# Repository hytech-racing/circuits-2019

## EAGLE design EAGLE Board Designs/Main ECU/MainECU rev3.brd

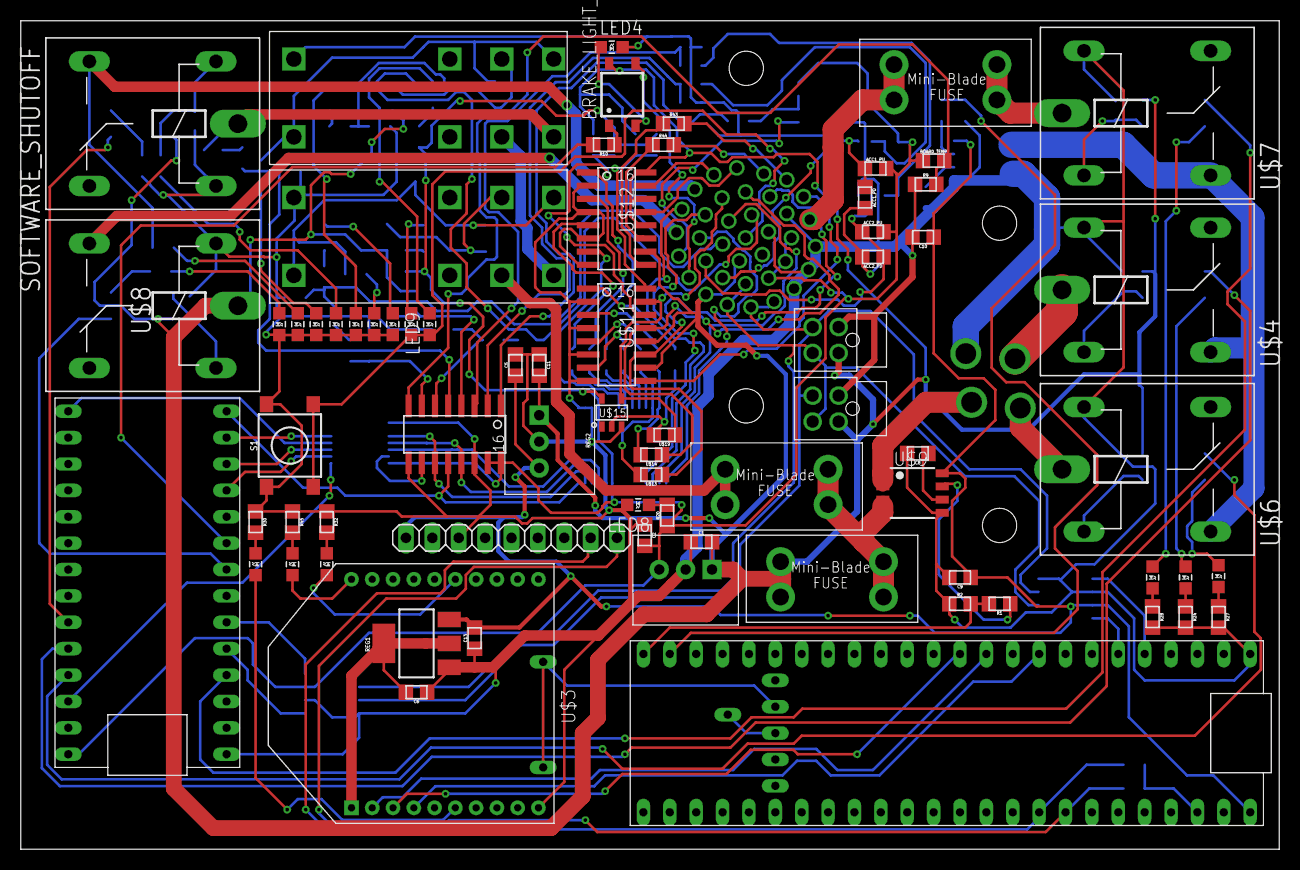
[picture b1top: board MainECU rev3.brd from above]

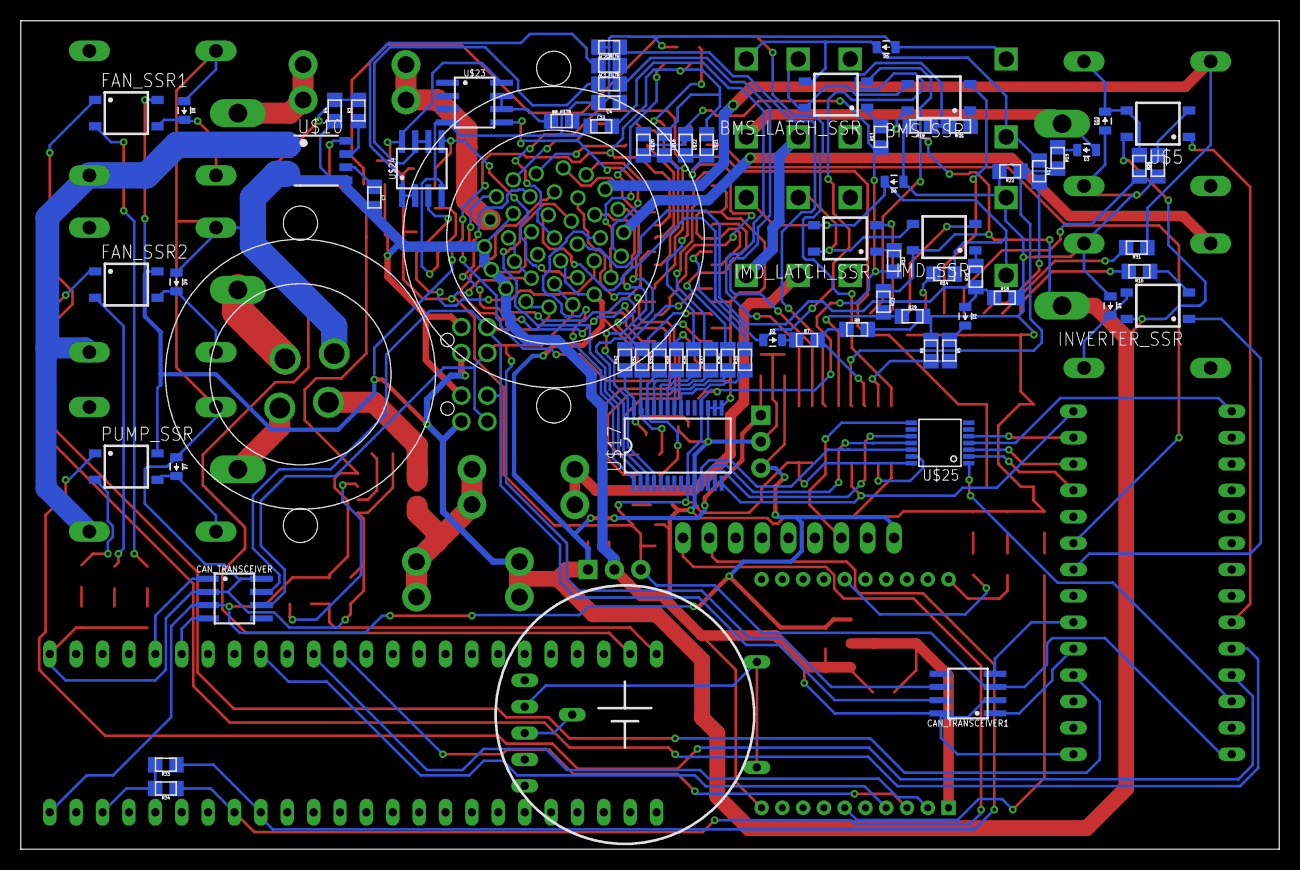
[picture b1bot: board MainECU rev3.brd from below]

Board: 2 copper layers, 121.2 x 79.8 mm, 145 parts (72 on the bottom side), 145 nets.

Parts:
5ABOARDFUSE, 5AFUSE, 5ASHUTDOWNFUSE: MINI-BLADE_FUSE_HOLDER
AC1_FILTR, AC2_FILTR: 510; 0805
ACC1_PD, ACC1_PU, ACC2_PD, ACC2_PU: 10k; 0805
ADXL345_BREAKOUT: 1X09
BMS_LATCH_SSR: CPC1002N; SOP04
BMS_SSR: CPC1002N; SOP04
BOARD_TEMP: THERMISTOR_NCP210805; 0805
BRAKE_LIGHT_SSR: CPC1002N; SOP04
BR_FILTR: 100; 0805
C1, C2, C11, C13: 10uF; 0805
C3, C4: 22µ; 0805
C5, C6: 1uF; 0805
C7, C8: 0805
C9, C10: 0.1uF; 0805
C12: 2.2µ; 0805
CAN_TRANSCEIVER, CAN_TRANSCEIVER1: MCP2551; SOIC-08
D1, D2, D3, D4, D5, D6, D7, D8, D9, D10: DIODE0805; 0805_D
FAN_SSR1, FAN_SSR2: CPC1002N; SOP04
IMD_LATCH_SSR: CPC1002N; SOP04
IMD_SHUTDOWN, IMD_SHUTDOWN1: G2RL-2-DC12; G2RL-2
IMD_SSR: CPC1002N; SOP04
INVERTER_SSR: CPC1002N; SOP04
LED1, LED2: White; LED-805
LED3, LED7, LED11: Green; LED-805
LED4, LED6, LED10, LED12, LED13, LED16: Red; LED-805
LED5, LED9: Yellow; LED-805
LED8: Purple; LED-805
LED14: Blue; LED-805
LED17, LED18: RED; LED-805
PUMP_SSR: CPC1002N; SOP04
R1, R3: 1K; 0805
R2, R4: 2K; 0805
R5, R7, R15, R23: 43k; 0805
R6, R8, R22, R29: 12k; 0805
R9, R19: 10k; 0805
R10, R16: 43; 0805
R11: 150; 0805
R12, R13, R24, R27, R28, R30: 33; 0805
R14, R21: 2k; 0805
R17: 20k; 0805
R18: 2.2k; 0805
R20, R35, R36, R37, R38, R39, R40, R41, R42: 270; 0805
R25: 330; 0805
R26: 1.2K; 0805
R31: 6.8k; 0805
R32: 1.2k; 0805
R33, R34: 4.7k; 0805
R43, R44, R45: 0; 0805
REG, REG2: 5V; OKI-78SR
REG1: TLV1117LV33; SOT223
S1: TACTILE_SWITCH_SMD_6.2MM_TALL
SOFTWARE_SHUTOFF: G5LE; ZF112
U$1: TEENSY_3.2_SIMPLE
U$2: TEENSY_3.5_EXT
U$3: XBEE
U$4, U$6, U$7, U$8: G5LE; ZF112
U$5: CPC1002N; SOP04
U$9, U$10: ACS715_CURRENT_SENSOR; SOP8
U$11, U$12: TLP291-4; SOIC-16
U$13, U$14, U$16, U$19, U$20, U$21, U$22: JUMPER; 0805
U$15: SN74LV1T34; SOT-23-5
U$17: MCP23S17SSOP28; SSOP28
U$18: MCP3208SOIC; SOIC-16
U$23, U$24: MCP6002SOIC; SOIC-08
U$25: TXB0104TSSOP; TSSOP-14
U$26: CR-2450/G1AN
X1: CONNECTOR-37; AUTOSPORT_14-35
X2: CONNECTOR-4AUTOSPORT; AUTOSPORT_12-04
X3, X4: CONNECTOR-4NANO-FIT-VERTICAL-4; NANO-FIT_VERTICAL-4

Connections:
3.3V: R33.2, R34.2, U$2.3.3V
3.3V_MAIN_TEENSY: U$1.3.3V, U$25.1
12VIN: U$9.1, U$9.2, X2.P$1
12VSUPPLY_READ: R23.2, R29.1, U$18.4
12VUNFUSED: 5ABOARDFUSE.L1, 5ABOARDFUSE.L2, 5ASHUTDOWNFUSE.L1, 5ASHUTDOWNFUSE.L2, U$9.3, U$9.4
+5V: ACC1_PU.2, ACC2_PU.2, BOARD_TEMP.1, C2.2, CAN_TRANSCEIVER1.3, R12.2, R13.1, R20.1, REG.3, U$1.VIN, U$15.5, U$17.9, U$17.18, U$18.15, U$18.16, U$20.1, U$22.1, U$23.8, U$24.8, U$25.14, X1.P$27, X1.P$28, X1.P$29
+12V: 5ABOARDFUSE.R1, 5ABOARDFUSE.R2, BMS_SSR.4, BRAKE_LIGHT_SSR.4, C1.2, C11.2, FAN_SSR1.4, FAN_SSR2.4, IMD_SSR.4, INVERTER_SSR.4, PUMP_SSR.4, R23.1, REG.1, REG2.1, U$5.4, U$8.P, U$11.10, U$11.12, U$12.10, U$12.12, U$12.14, U$12.16, U$16.1, U$21.1, X1.P$10, X1.P$34, X3.P$1, X4.P$1
BMS_COIL_PWR: BMS_LATCH_SSR.3, D5.C, IMD_SHUTDOWN1.4, IMD_SHUTDOWN1.COIL-, R17.1
BMS_OK: D2.A, R11.2, R19.1, X1.P$31
BMS_OK_READ: R7.2, R8.1, U$18.6
BMS_PWR_STEP: BMS_LATCH_SSR.4, BMS_SSR.3, IMD_SHUTDOWN1.3
BRAKE_LIGHT: BRAKE_LIGHT_SSR.3, X1.P$9
BRAKE_LIGHT_CTRL: R10.2, U$1.D7(RX3)
CANH: CAN_TRANSCEIVER.7, CAN_TRANSCEIVER1.7, X1.P$12, X1.P$13, X3.P$4, X4.P$4
CANL: CAN_TRANSCEIVER.6, CAN_TRANSCEIVER1.6, X1.P$11, X1.P$26, X3.P$3, X4.P$3
COOLINGSENSE: R3.2, R4.2, U$2.A12
CS1_5V: U$18.10, U$25.13
CS1_TEENSY: U$1.D9(RX2), U$25.2
CS2_5V: U$17.11, U$25.12
CS2_TEENSY: U$1.D10(TX2), U$25.3
CURRENTSENSE2: U$4.S, U$6.S, U$7.S, U$10.1, U$10.2
DASH_CTRL1: R35.1, U$17.21
DASH_CTRL2: R36.1, U$17.22
DASH_CTRL3: R37.1, U$17.23
DASH_CTRL4: R38.1, U$17.24
DASH_CTRL5: R39.1, U$17.25
DASH_CTRL6: R40.1, U$13.2, U$17.26
DASH_CTRL7: R41.1, U$14.2, U$17.27
DASH_CTRL8: R42.1, U$15.2, U$17.28, U$19.2
DASH_CTRL9: U$17.1, X1.P$23
DASH_CTRL10: U$17.2, X1.P$32
DASH_CTRL11: U$17.3, X1.P$6
DASH_CTRL12: U$17.4, X1.P$22
DASH_IO1: R43.2, X1.P$1
DASH_IO2: R44.2, X1.P$2
DASH_IO3: U$12.13, X1.P$3
DASH_IO4: U$12.15, X1.P$4
DASH_IO5: U$11.9, X1.P$18
DASH_IO6: U$11.11, U$13.1, X1.P$19
DASH_IO7: U$11.13, U$14.1, X1.P$20
DASH_IO8: U$11.15, U$15.4, U$19.1, X1.P$21
ECUSENSE: R1.2, R2.2, U$2.A13
FAN1-: 5AFUSE.R1, 5AFUSE.R2, U$7.P
FAN2-: U$4.P, X2.P$3
GND: ACC1_PD.2, ACC2_PD.2, ADXL345_BREAKOUT.3, C1.1, C2.1, C3.2, C4.2, C5.2, C6.1, C7.2, C8.2, C9.2, C10.2, C11.1, C12.1, C13.1, CAN_TRANSCEIVER.2, CAN_TRANSCEIVER.8, CAN_TRANSCEIVER1.2, CAN_TRANSCEIVER1.8, D4.A, D5.A, D6.A, D7.A, D8.A, D9.A, D10.A, IMD_SHUTDOWN.COIL+, IMD_SHUTDOWN1.COIL+, LED3.C, LED4.C, LED5.C, LED6.C, LED7.C, LED8.C, LED9.C, LED17.C, LED18.C, R2.1, R4.1, R6.2, R8.2, R9.1, R18.2, R19.2, R22.2, R24.2, R25.1, R27.2, R28.2, R29.2, R30.1, R32.1, R45.1, REG.2, REG1.1, REG2.2, S1.B1, S1.B2, SOFTWARE_SHUTOFF.1, U$1.GND, U$2.GND, U$3.10, U$4.1, U$6.1, U$7.1, U$8.2, U$9.5, U$10.3, U$10.4, U$10.5, U$11.2, U$11.4, U$11.6, U$11.8, U$12.2, U$12.4, U$12.6, U$12.8, U$15.3, U$17.10, U$17.15, U$17.16, U$17.17, U$18.9, U$18.14, U$23.4, U$24.4, U$25.8, X1.P$14, X1.P$15, X1.P$16, X1.P$30, X1.P$36, X2.P$4, X3.P$2, X4.P$2
IMD_COIL_PWR: D6.C, IMD_LATCH_SSR.3, IMD_SHUTDOWN.4, IMD_SHUTDOWN.COIL-, R14.1
IMD_PWR_STEP: IMD_LATCH_SSR.4, IMD_SHUTDOWN.3, IMD_SSR.3
INVERTER_CTRL: INVERTER_SSR.1, U$1.D6
INVERTER_SUPPLY: U$8.S, X1.P$7
LATCH_EXT_BUTTON: LED1.C, LED2.C, S1.A1, S1.A2, X1.P$37
MISO_TEENSY: U$1.D12, U$17.14, U$18.12
MOSI_5V: U$17.13, U$18.11, U$25.10
MOSI_TEENSY: U$1.D11, U$25.5
unnamed: 5AFUSE.L1, 5AFUSE.L2, X1.P$17
unnamed: IMD_LATCH_SSR.2, LED1.A
unnamed: R1.1, U$9.7
unnamed: D7.C, PUMP_SSR.3, U$6.2
unnamed: IMD_LATCH_SSR.1, R12.1
unnamed: R3.1, U$10.7
unnamed: BRAKE_LIGHT_SSR.2, LED4.A
unnamed: C8.1, U$9.6
unnamed: BMS_SSR.2, LED3.A
unnamed: D1.C, R5.1
unnamed: D2.C, R7.1
unnamed: BMS_LATCH_SSR.1, R13.2
unnamed: CAN_TRANSCEIVER.4, U$2.D4(CANRX)
unnamed: CAN_TRANSCEIVER.1, U$2.D3(CANTX)
unnamed: CAN_TRANSCEIVER1.4, U$1.D4(CANRX)
unnamed: BMS_LATCH_SSR.2, LED2.A
unnamed: BRAKE_LIGHT_SSR.1, R10.1
unnamed: BMS_SSR.1, R11.1
unnamed: LED5.A, R14.2
unnamed: D8.C, FAN_SSR1.3, U$7.2
unnamed: D9.C, FAN_SSR2.3, U$4.2
unnamed: CAN_TRANSCEIVER1.1, U$1.D3(CANTX)
unnamed: AC2_FILTR.1, U$24.1, U$24.2
unnamed: AC1_FILTR.1, U$24.6, U$24.7
unnamed: BR_FILTR.1, U$23.6, U$23.7
unnamed: D4.C, INVERTER_SSR.3, U$8.1
unnamed: INVERTER_SSR.2, R16.1
unnamed: LED6.A, R16.2
unnamed: LED8.A, R20.2
unnamed: LED16.C, R24.1
unnamed: IMD_SSR.1, R21.2
unnamed: LED7.A, R17.2
unnamed: D3.C, R15.1
unnamed: IMD_SSR.2, LED9.A
unnamed: LED14.C, R45.2
unnamed: LED13.C, R28.1
unnamed: LED12.C, R27.1
unnamed: LED12.A, PUMP_SSR.2
unnamed: FAN_SSR2.2, LED16.A
unnamed: LED18.A, R31.2
unnamed: U$2.3.3V_2, U$26.+_0, U$26.+_1
unnamed: FAN_SSR1.2, LED13.A
unnamed: D10.C, R26.1, SOFTWARE_SHUTOFF.2, U$5.3
unnamed: R25.2, U$5.2
unnamed: LED11.C, R30.2
unnamed: LED17.A, R26.2
unnamed: LED11.A, U$3.6
unnamed: C7.1, U$10.6
unnamed: LED10.A, U$3.15
unnamed: LED10.C, R32.2
unnamed: R35.2, U$12.7
unnamed: R36.2, U$12.5
unnamed: R37.2, U$12.3
unnamed: R38.2, U$12.1
unnamed: R39.2, U$11.7
unnamed: R40.2, U$11.5
unnamed: R41.2, U$11.3
unnamed: R42.2, U$11.1
unnamed: R43.1, U$12.9
unnamed: R44.1, U$12.11
unnamed: U$11.16, U$16.2, U$20.2
unnamed: U$11.14, U$21.2, U$22.2
unnamed: LED14.A, U$3.20
unnamed: U$2.GND_2, U$26.-
OKHS: D1.A, R18.1, R21.1, X1.P$33
OKHS_READ: R5.2, R6.1, U$18.7
PUMP1-: U$6.P, X2.P$2
READ_ACCEL1: AC1_FILTR.2, C4.1, U$18.2
READ_ACCEL2: AC2_FILTR.2, C3.1, U$18.3
READ_BRAKE: BR_FILTR.2, C12.2, U$18.1
RELAY_CTRL1: PUMP_SSR.1, U$1.A9
RELAY_CTRL2: FAN_SSR1.1, U$1.D2
RELAY_CTRL3: FAN_SSR2.1, U$1.A8
SCK_5V: U$17.12, U$18.13, U$25.11
SCK_TEENSY: U$1.D13, U$25.4
SCL: ADXL345_BREAKOUT.9, R34.1, U$2.A5
SDA: ADXL345_BREAKOUT.8, R33.1, U$2.A4
SHUTDOWN_A: 5ASHUTDOWNFUSE.R1, 5ASHUTDOWNFUSE.R2, IMD_SHUTDOWN.6
SHUTDOWN_B: IMD_SHUTDOWN.5, IMD_SHUTDOWN1.6
SHUTDOWN_C: D3.A, IMD_SHUTDOWN1.5, SOFTWARE_SHUTOFF.P
SHUTDOWN_D: R31.1, SOFTWARE_SHUTOFF.S, X1.P$5
SHUTDOWN_OUT_READ: R15.2, R22.1, U$18.5
SIGNAL_ACCEL1: ACC1_PD.1, ACC1_PU.1, U$24.5, X1.P$25
SIGNAL_ACCEL2: ACC2_PD.1, ACC2_PU.1, U$24.3, X1.P$24
SIGNAL_BRAKE: U$23.5, X1.P$8
SOFTWARE_SHUTDOWN: U$1.A7, U$5.1
TELEMETRY5V: ADXL345_BREAKOUT.1, C5.1, C9.1, C10.1, C13.2, CAN_TRANSCEIVER.3, REG1.3, REG2.3, U$2.VIN, U$9.8, U$10.8
TEMPSENSE: BOARD_TEMP.2, R9.2, U$18.8
VCC: C6.2, REG1.2, REG1.4, U$3.1
XB8: U$2.D7(RX3), U$3.4
XBDI: U$2.D10(TX2), U$3.3
XBDO: U$2.D9(RX2), U$3.2

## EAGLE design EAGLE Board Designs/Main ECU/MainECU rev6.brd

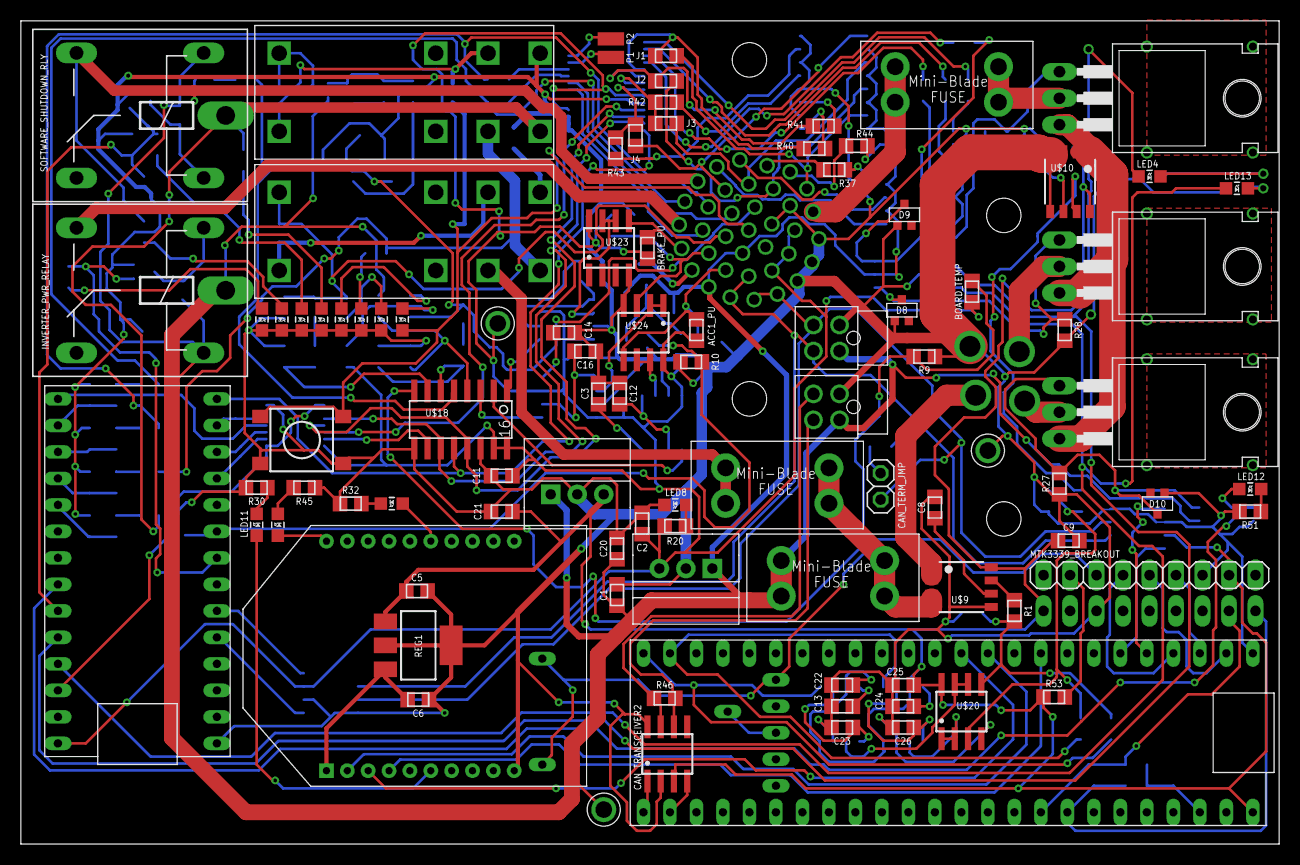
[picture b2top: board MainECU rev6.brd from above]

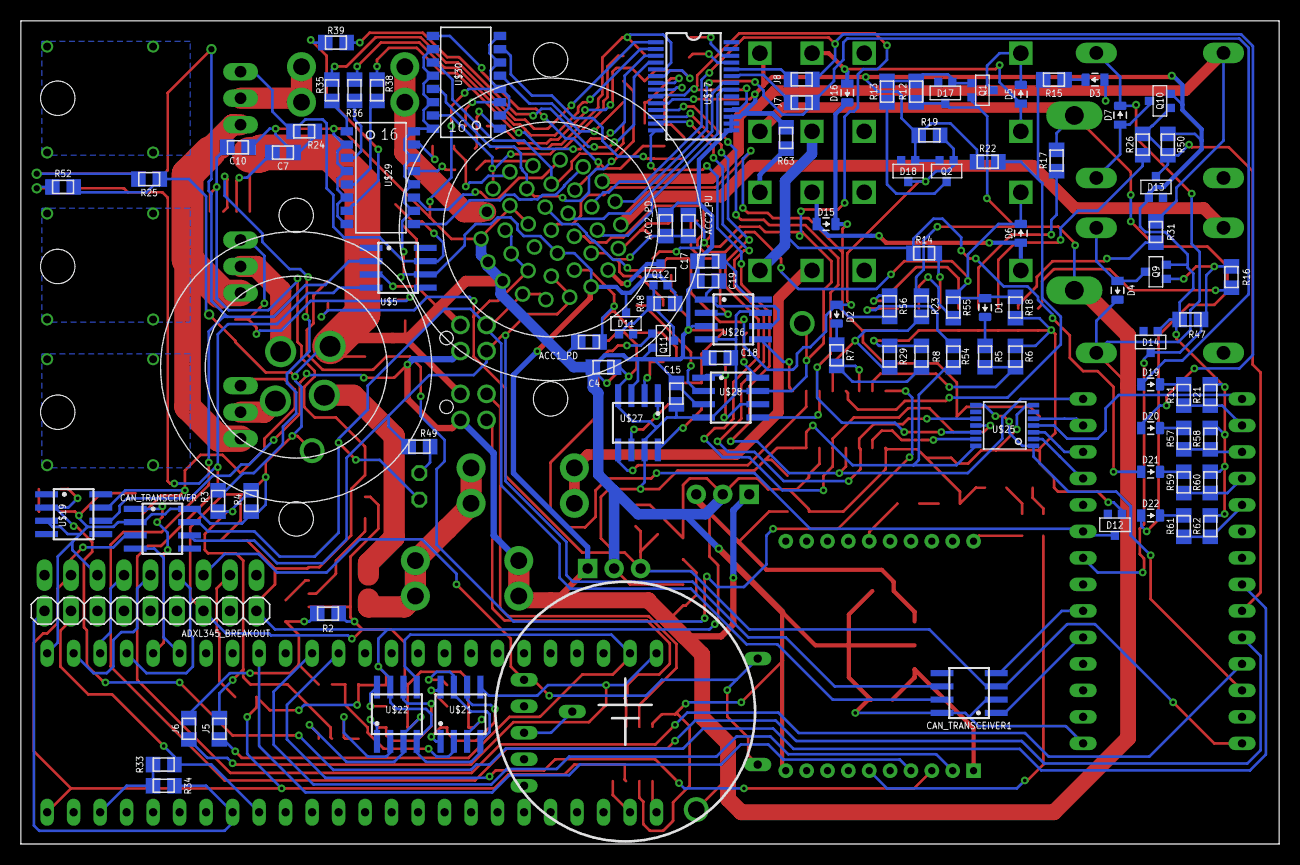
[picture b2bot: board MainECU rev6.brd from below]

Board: 2 copper layers, 120.6 x 78.9 mm, 196 parts (101 on the bottom side), 169 nets.

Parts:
5ABOARDFUSE, 5AFUSE, 5ASHUTDOWNFUSE: MINI-BLADE_FUSE_HOLDER
ACC1_PD, ACC1_PU, ACC2_PD, ACC2_PU: 10k; 0805
ADXL345_BREAKOUT: 1X09
BMS_SHUTDOWN_RLY: RT424012; RELAY_DPDT
BOARD_TEMP: THERMISTOR_NCP210805; 0805
BRAKE_PU: 10k; 0805
C1, C2, C20, C21: 10uF; 0805
C3, C7, C8, C14, C17: 47nF; 0805
C4, C12, C15, C16, C18, C19, C22, C23, C25, C26: .1uF; 0805
C5, C6, C11: 1uF; 0805
C9, C10: 0.1uF; 0805
C13, C24: 470pF; 0805
CAN_TERM_JMP: M02_SLIM; 1X02_SLIM
CAN_TRANSCEIVER, CAN_TRANSCEIVER1, CAN_TRANSCEIVER2: MCP2551; SOIC-08
D1, D2, D3, D4, D5, D6, D7, D15, D16, D19, D20, D21, D22: TS4148 RYG; 0805_D
D8, D9, D10, D11, D12, D13, D14, D17, D18: MMBZ5246BLT1G; SOT23
IMD_SHUTDOWN_RLY: RT424009; RELAY_DPDT
INVERTER_PWR_RELAY: G5LE; ZF112
J1, J2, J3, J4, J5, J6, J7, J8: JUMPER; 0805
LED1: White; LED-805
LED3, LED7, LED11: Green; LED-805
LED4, LED6, LED10, LED12, LED13, LED17, LED18: Red; LED-805
LED5, LED9: Yellow; LED-805
LED8: Purple; LED-805
LED14: Blue; LED-805
MTK3339_BREAKOUT: 1X09
P1, P2: SOLDER_PAD; SOLDER_PAD_XSMALL
Q1, Q12: P-CHANNEL_MOSFET_DMP3099L-7; SOT23
Q2, Q9, Q10, Q11: SOT23
R1, R3: 1K; 0805
R2, R4: 2K; 0805
R5, R7, R11, R15, R23, R57, R59, R61: 43k; 0805
R6, R8, R21, R22, R29, R58, R60, R62: 12k; 0805
R9, R10, R12, R19, R24, R27, R28, R47, R48, R50, R53: 10k; 0805
R13: 1k; 0805
R14, R18, R55: 2k; 0805
R16, R25, R32, R51, R52: 1.2k; 0805
R17: 20k; 0805
R20: 270; 0805
R26: 1.2K; 0805
R30, R56: 33; 0805
R31: 6.8k; 0805
R33, R34: 4.7k; 0805
R35, R36, R38, R39, R40, R41, R42, R43: 150; 0805
R37, R44, R45: 0; 0805
R46, R49: 120; 0805
R54: 5.1k; 0805
R63: 20; 0805
REG, REG3: 5V; OKI-78SR
REG1: LM3940; SOT223
S1: TACTILE_SWITCH_SMD_6.2MM_TALL
SOFTWARE_SHUTDOWN_RLY: G5LE; ZF112
U$1: TEENSY_3.2_SIMPLE
U$2: TEENSY_3.5_EXT
U$3: XBEE
U$4, U$6, U$7: N-CHANNEL_MOSFET_FQP30N06L; TO-220-H-HOLE
U$5, U$19: MC34152; SOIC-08
U$8, U$11, U$12: TEST_POINT
U$9, U$10: ACS715_CURRENT_SENSOR; SOP8
U$16: CR-2450/G1AN
U$17: MCP23S17SSOP28; SSOP28
U$18: MCP3208SOIC; SOIC-16
U$20, U$23, U$24: MCP6002SOIC; SOIC-08
U$21, U$22, U$26, U$27, U$28: SOIC-08
U$25: TXB0104TSSOP; TSSOP-14
U$29, U$30: TLP291-4; 11-11F1
X1: CONNECTOR-37; AUTOSPORT_14-35
X2: CONNECTOR-4AUTOSPORT; AUTOSPORT_12-04
X3, X4: CONNECTOR-4NANO-FIT-VERTICAL-4; NANO-FIT_VERTICAL-4

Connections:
3.3V: R33.2, R34.2, U$2.3.3V
3.3V_MAIN_TEENSY: U$1.3.3V, U$25.1, U$25.8
12VIN: U$9.1, U$9.2, X2.P$1
12VSUPPLY_READ: R23.2, R29.1, U$18.4
12VUNFUSED: 5ABOARDFUSE.L1, 5ABOARDFUSE.L2, 5ASHUTDOWNFUSE.L1, 5ASHUTDOWNFUSE.L2, U$9.3, U$9.4
+5V: ACC1_PU.2, ACC2_PU.2, BOARD_TEMP.1, BRAKE_PU.2, C2.2, C4.1, C11.2, C15.1, C18.1, CAN_TRANSCEIVER1.3, R20.1, R54.1, REG.3, U$1.VIN, U$11.P$1, U$17.9, U$17.18, U$18.15, U$18.16, U$23.8, U$24.8, U$25.14, U$26.4, U$26.7, U$27.4, U$27.7, U$28.4, U$28.7, X1.P$27, X1.P$28, X1.P$29
+12V: 5ABOARDFUSE.R1, 5ABOARDFUSE.R2, C1.2, C20.2, D4.C, D7.C, D11.3, D17.3, INVERTER_PWR_RELAY.1, INVERTER_PWR_RELAY.P, Q1.2, Q12.2, R12.1, R23.1, R48.1, REG.1, REG3.1, SOFTWARE_SHUTDOWN_RLY.2, U$5.6, U$8.P$1, U$19.6, U$29.10, U$29.12, U$29.14, U$29.16, U$30.10, U$30.12, U$30.14, U$30.16, X1.P$10, X1.P$34, X3.P$1, X4.P$1
BMS_OK: D2.A, D18.3, Q2.1, R19.1, R56.1, X1.P$31
BMS_OK_READ: R7.2, R8.1, U$18.6
BMS_OK_SW: BMS_SHUTDOWN_RLY.COIL+, D5.C, Q1.3
BMS_PWR_STEP: BMS_SHUTDOWN_RLY.3, BMS_SHUTDOWN_RLY.COIL-, D5.A, D16.A
BRAKE_LIGHT: Q12.3, X1.P$9
BRAKE_LIGHT_CTRL: D12.3, Q11.1, R10.2, U$1.D7(RX3)
CANH: CAN_TERM_JMP.1, CAN_TRANSCEIVER.7, CAN_TRANSCEIVER1.7, X1.P$12, X1.P$13, X3.P$4
CANL: CAN_TRANSCEIVER.6, CAN_TRANSCEIVER1.6, R49.1, X1.P$11, X1.P$26, X3.P$3
COOLINGSENSE: J5.2, R3.2, R4.2, U$20.3
COOLINGSENSE_FILT: J5.1, U$2.A12, U$22.5
CS1_5V: U$18.10, U$25.13
CS1_TEENSY: U$1.D9(RX2), U$25.2
CS2_5V: U$17.11, U$25.12
CS2_TEENSY: U$1.D10(TX2), U$25.3
CURRENTSENSE2: U$4.3, U$6.3, U$7.3, U$10.1, U$10.2
DASH11_READ: R11.2, R21.1, U$1.A0
DASH12_READ: R57.2, R58.1, U$1.A1
DASH_1_EXTERN: R44.2, X1.P$1
DASH_1_INTER: R35.1, U$17.1
DASH_2_EXTERN: R37.2, X1.P$2
DASH_2_INTER: R36.1, U$17.2
DASH_3_EXTERN: U$29.11, X1.P$3
DASH_3_INTER: R38.1, U$17.3
DASH_4_EXTERN: U$29.9, X1.P$4
DASH_4_INTER: R39.1, U$17.4
DASH_5_EXTERN: J1.1, U$30.15, X1.P$18
DASH_5_INTER: J1.2, R40.1, U$17.5
DASH_6_EXTERN: J2.1, U$30.13, X1.P$19
DASH_6_INTER: J2.2, R41.1, U$17.6
DASH_7_EXTERN: J3.1, U$30.11, X1.P$20
DASH_7_INTER: J3.2, R42.1, U$17.7
DASH_8_EXTERN: J4.1, U$30.9, X1.P$21
DASH_8_INTER: J4.2, R43.1, U$17.8
DASH_9_EXTERN: U$17.21, X1.P$23
DASH_10_EXTERN: U$17.22, X1.P$32
DASH_11_EXTERN: D19.A, J7.1, X1.P$6
DASH_11_INTER: J7.2, U$17.23
DASH_12_EXTERN: D20.A, J8.1, X1.P$22
DASH_12_INTER: J8.2, U$17.24
ECUSENSE: J6.2, R1.2, R2.2, U$20.5
ECUSENSE_FILT: J6.1, U$2.A13, U$21.5
FAN1-: 5AFUSE.R1, 5AFUSE.R2, U$7.2
FAN1CONTROL: LED4.A, U$1.A8, U$5.2
FAN1DRIVE: D9.3, R24.2, U$5.7, U$7.1
FAN2-: U$4.2, X2.P$3
FAN2CONTROL: LED13.A, U$1.A9, U$5.4
FAN2DRIVE: D8.3, R28.2, U$4.1, U$5.5
GND: ACC1_PD.2, ACC2_PD.2, ADXL345_BREAKOUT.3, BMS_SHUTDOWN_RLY.4, C1.1, C2.1, C3.2, C4.2, C5.2, C6.1, C7.2, C8.2, C9.2, C10.2, C11.1, C12.1, C13.2, C14.2, C15.2, C16.1, C17.2, C18.2, C19.1, C20.1, C21.1, C22.2, C23.1, C24.2, C25.2, C26.1, CAN_TRANSCEIVER.2, CAN_TRANSCEIVER.8, CAN_TRANSCEIVER1.2, CAN_TRANSCEIVER1.8, CAN_TRANSCEIVER2.2, CAN_TRANSCEIVER2.8, D8.1, D9.1, D10.1, D12.1, D13.1, D14.1, D18.1, LED3.C, LED5.C, LED6.C, LED7.C, LED8.C, LED9.C, LED17.C, LED18.C, MTK3339_BREAKOUT.7, Q2.2, Q9.2, Q10.2, Q11.2, R2.1, R4.1, R6.2, R8.2, R9.1, R10.1, R18.2, R19.2, R21.2, R22.2, R24.1, R25.2, R27.1, R28.1, R29.2, R30.1, R32.1, R45.1, R47.2, R50.2, R51.2, R52.2, R58.2, R60.2, R62.2, R63.2, REG.2, REG1.2, REG1.4, REG3.2, S1.B1, S1.B2, U$1.GND, U$2.GND, U$3.10, U$5.3, U$9.5, U$10.3, U$10.4, U$10.5, U$12.P$1, U$17.10, U$17.15, U$17.16, U$17.17, U$18.9, U$18.14, U$19.3, U$20.4, U$21.3, U$22.3, U$23.4, U$24.4, U$25.7, U$26.3, U$27.3, U$28.3, U$29.2, U$29.4, U$29.6, U$29.8, U$30.2, U$30.4, U$30.6, U$30.8, X1.P$14, X1.P$15, X1.P$16, X1.P$30, X1.P$36, X2.P$4, X3.P$2, X4.P$2
IMD_PWR_STEP: D6.A, D15.A, IMD_SHUTDOWN_RLY.3, IMD_SHUTDOWN_RLY.COIL-
INVERTER_CTRL: D14.3, Q9.1, R16.1, R47.1, U$1.D6
INVERTER_SUPPLY: INVERTER_PWR_RELAY.S, X1.P$7
LATCH_EXT_BUTTON: D15.C, D16.C, LED1.C, S1.A1, S1.A2, X1.P$37
MISO_TEENSY: U$1.D12, U$17.14, U$18.12
MOSI_5V: U$17.13, U$18.11, U$25.10
MOSI_TEENSY: U$1.D11, U$25.5
MTK3339_DIN: MTK3339_BREAKOUT.6, U$2.D1(TX1)
MTK3339_DOUT: MTK3339_BREAKOUT.5, U$2.D0(RX1)
MTK3339_FIX: MTK3339_BREAKOUT.4, U$2.D2
unnamed: 5AFUSE.L1, 5AFUSE.L2, X1.P$17
unnamed: LED1.A, R54.2
unnamed: R1.1, U$9.7
unnamed: C12.2, U$27.1, U$27.6
unnamed: D20.C, R57.1
unnamed: R3.1, U$10.7
unnamed: MTK3339_BREAKOUT.2, R53.2
unnamed: C8.1, U$9.6
unnamed: LED3.A, R56.2
unnamed: D1.C, R5.1
unnamed: D2.C, R7.1
unnamed: D17.1, Q1.1, R12.2, R13.2
unnamed: CAN_TRANSCEIVER.4, U$2.D4(CANRX)
unnamed: CAN_TRANSCEIVER.1, U$2.D3(CANTX)
unnamed: CAN_TRANSCEIVER1.4, U$1.D4(CANRX)
unnamed: Q2.3, R13.1
unnamed: CAN_TERM_JMP.2, R49.2
unnamed: D19.C, R11.1
unnamed: LED5.A, R14.2
unnamed: U$20.1, U$20.2, U$22.2
unnamed: C3.1, U$27.8
unnamed: CAN_TRANSCEIVER1.1, U$1.D3(CANTX)
unnamed: U$24.1, U$24.2, U$28.2
unnamed: U$24.6, U$24.7, U$27.2
unnamed: U$23.6, U$23.7, U$26.2
unnamed: LED9.A, R55.2
unnamed: D7.A, Q10.3, SOFTWARE_SHUTDOWN_RLY.1
unnamed: LED6.A, R16.2
unnamed: LED8.A, R20.2
unnamed: R36.2, U$29.3
unnamed: D21.C, R59.1
unnamed: LED7.A, R17.2
unnamed: D3.C, R15.1
unnamed: D22.C, R61.1
unnamed: LED14.C, R45.2
unnamed: C16.2, U$28.1, U$28.6
unnamed: C19.2, U$26.1, U$26.6
unnamed: C14.1, U$28.8
unnamed: U$20.6, U$20.7, U$21.2
unnamed: LED18.A, R31.2
unnamed: C17.1, U$26.8
unnamed: R37.1, U$29.13
unnamed: C23.2, U$21.1, U$21.6
unnamed: C13.1, U$21.8
unnamed: LED11.C, R30.2
unnamed: LED17.A, R26.2
unnamed: LED11.A, U$3.6
unnamed: C7.1, U$10.6
unnamed: LED10.A, U$3.15
unnamed: LED10.C, R32.2
unnamed: R35.2, U$29.1
unnamed: R38.2, U$29.5
unnamed: R39.2, U$29.7
unnamed: R40.2, U$30.1
unnamed: R41.2, U$30.3
unnamed: R42.2, U$30.5
unnamed: R43.2, U$30.7
unnamed: D11.1, Q11.3, Q12.1, R48.2
unnamed: R44.1, U$29.15
unnamed: IMD_SHUTDOWN_RLY.4, R63.1
unnamed: U$2.GND_2, U$16.-
unnamed: CAN_TRANSCEIVER2.4, U$2.A15
unnamed: LED14.A, U$3.20
unnamed: CAN_TRANSCEIVER2.1, U$2.A14
unnamed: D4.A, INVERTER_PWR_RELAY.2, Q9.3
unnamed: C26.2, U$22.1, U$22.6
unnamed: C24.1, U$22.8
unnamed: LED4.C, R25.1
unnamed: LED12.C, R51.1
unnamed: LED13.C, R52.1
unnamed: P1.P$1, U$17.25
unnamed: P2.P$1, U$17.26
OKHS: D1.A, D6.C, IMD_SHUTDOWN_RLY.COIL+, R18.1, R55.1, X1.P$33
OKHS_READ: R5.2, R6.1, U$18.7
PUMP1-: U$6.2, X2.P$2
PUMPCONTROL: LED12.A, U$1.A6, U$19.2
PUMPDRIVE: D10.3, R27.2, U$6.1, U$19.7
READ_ACCEL1: U$18.2, U$27.5
READ_ACCEL2: U$18.3, U$28.5
READ_BRAKE: U$18.1, U$26.5
SCK_5V: U$17.12, U$18.13, U$25.11
SCK_TEENSY: U$1.D13, U$25.4
SCL: ADXL345_BREAKOUT.9, R34.1, U$2.A5
SDA: ADXL345_BREAKOUT.8, R33.1, U$2.A4
SHUTDOWN_A: 5ASHUTDOWNFUSE.R1, 5ASHUTDOWNFUSE.R2, IMD_SHUTDOWN_RLY.6
SHUTDOWN_B: BMS_SHUTDOWN_RLY.6, D21.A, IMD_SHUTDOWN_RLY.5, R14.1
SHUTDOWN_B_READ: R59.2, R60.1, U$1.A2
SHUTDOWN_C: BMS_SHUTDOWN_RLY.5, D22.A, R17.1, SOFTWARE_SHUTDOWN_RLY.P
SHUTDOWN_C_READ: R61.2, R62.1, U$1.A3
SHUTDOWN_D: D3.A, R31.1, SOFTWARE_SHUTDOWN_RLY.S, X1.P$5
SHUTDOWN_OUT_READ: R15.2, R22.1, U$18.5
SIGNAL_ACCEL1: ACC1_PD.1, ACC1_PU.1, U$24.5, X1.P$25
SIGNAL_ACCEL2: ACC2_PD.1, ACC2_PU.1, U$24.3, X1.P$24
SIGNAL_BRAKE: BRAKE_PU.1, U$23.5, X1.P$8
SOFTWARE_SHUTDOWN: D13.3, Q10.1, R26.1, R50.1, U$1.A7
TELEMETRY5V: ADXL345_BREAKOUT.1, C5.1, C9.1, C10.1, C21.2, C22.1, C25.1, CAN_TRANSCEIVER.3, CAN_TRANSCEIVER2.3, MTK3339_BREAKOUT.8, R53.1, REG1.1, REG3.3, U$2.VIN, U$9.8, U$10.8, U$20.8, U$21.4, U$21.7, U$22.4, U$22.7
TELEMETRY_CANH: CAN_TRANSCEIVER2.7, R46.2, X4.P$4
TELEMETRY_CANL: CAN_TRANSCEIVER2.6, R46.1, X4.P$3
TEMPSENSE: BOARD_TEMP.2, R9.2, U$18.8
VBAT_RTC: MTK3339_BREAKOUT.3, U$2.VBAT, U$16.+_0, U$16.+_1
VCC: C6.2, REG1.3, U$3.1
XB8: U$2.D7(RX3), U$3.4
XBDI: U$2.D10(TX2), U$3.3
XBDO: U$2.D9(RX2), U$3.2

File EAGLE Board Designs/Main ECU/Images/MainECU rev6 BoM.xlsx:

Part | Value | Device | Package
5ABOARDFUSE |  | FUSE_MINIBLADE | MINI-BLADE_FUSE_HOLDER
5AFUSE |  | FUSE_MINIBLADE | MINI-BLADE_FUSE_HOLDER
5ASHUTDOWNFUSE |  | FUSE_MINIBLADE | MINI-BLADE_FUSE_HOLDER
ACC1_PD | 10k | RESISTOR0805-RES | 805
ACC1_PU | 10k | RESISTOR0805-RES | 805
ACC2_PD | 10k | RESISTOR0805-RES | 805
ACC2_PU | 10k | RESISTOR0805-RES | 805
ADXL345_BREAKOUT |  | M09 | 1X09
BMS_SHUTDOWN_RLY | RT424012 | RT424012 | RELAY_DPDT
BOARD_TEMP | THERMISTOR_NCP210805 | THERMISTOR_NCP210805 | 805
BRAKE_PU | 10k | RESISTOR0805-RES | 805
C1 | 10uF | CAP0805 | 805
C2 | 10uF | CAP0805 | 805
C3 | 47nF | CAP0805 | 805
C4 | .1uF | CAP0805 | 805
C5 | 1uF | CAP0805 | 805
C6 | 1uF | CAP0805 | 805
C7 | 47nF | CAP0805 | 805
C8 | 47nF | CAP0805 | 805
C9 | 0.1uF | CAP0805 | 805
C10 | 0.1uF | CAP0805 | 805
C11 | 1uF | CAP0805 | 805
C12 | .1uF | CAP0805 | 805
C13 | 470pF | CAP0805 | 805
C14 | 47nF | CAP0805 | 805
C15 | .1uF | CAP0805 | 805
C16 | .1uF | CAP0805 | 805
C17 | 47nF | CAP0805 | 805
C18 | .1uF | CAP0805 | 805
C19 | .1uF | CAP0805 | 805
C20 | 10uF | CAP0805 | 805
C21 | 10uF | CAP0805 | 805
C22 | .1uF | CAP0805 | 805
C23 | .1uF | CAP0805 | 805
C24 | 470pF | CAP0805 | 805
C25 | .1uF | CAP0805 | 805
C26 | .1uF | CAP0805 | 805
CAN_TERM_JMP | M02_SLIM | M02_SLIM | 1X02_SLIM
CAN_TRANSCEIVER | MCP2551 | MCP2551 | SOIC-08
CAN_TRANSCEIVER1 | MCP2551 | MCP2551 | SOIC-08
CAN_TRANSCEIVER2 | MCP2551 | MCP2551 | SOIC-08
D1 | TS4148 RYG | DIODE0805 | 0805_D
D2 | TS4148 RYG | DIODE0805 | 0805_D
D3 | TS4148 RYG | DIODE0805 | 0805_D
D4 | TS4148 RYG | DIODE0805 | 0805_D
D5 | TS4148 RYG | DIODE0805 | 0805_D
D6 | TS4148 RYG | DIODE0805 | 0805_D
D7 | TS4148 RYG | DIODE0805 | 0805_D
D8 | MMBZ5246BLT1G | DIODE_ZENER | SOT23
D9 | MMBZ5246BLT1G | DIODE_ZENER | SOT23
D10 | MMBZ5246BLT1G | DIODE_ZENER | SOT23
D11 | MMBZ5246BLT1G | DIODE_ZENER | SOT23
D12 | MMBZ5246BLT1G | DIODE_ZENER | SOT23
D13 | MMBZ5246BLT1G | DIODE_ZENER | SOT23
D14 | MMBZ5246BLT1G | DIODE_ZENER | SOT23
D15 | TS4148 RYG | DIODE0805 | 0805_D
D16 | TS4148 RYG | DIODE0805 | 0805_D
D17 | MMBZ5246BLT1G | DIODE_ZENER | SOT23
D18 | MMBZ5246BLT1G | DIODE_ZENER | SOT23
D19 | TS4148 RYG | DIODE0805 | 0805_D
D20 | TS4148 RYG | DIODE0805 | 0805_D
D21 | TS4148 RYG | DIODE0805 | 0805_D
D22 | TS4148 RYG | DIODE0805 | 0805_D
IMD_SHUTDOWN_RLY | RT424009 | RT424009 | RELAY_DPDT
INVERTER_PWR_RELAY | G5LE | G5LE | ZF112
J1 | JUMPER | JUMPER | 805
J2 | JUMPER | JUMPER | 805
J3 | JUMPER | JUMPER | 805
J4 | JUMPER | JUMPER | 805
J5 | JUMPER | JUMPER | 805
J6 | JUMPER | JUMPER | 805
J7 | JUMPER | JUMPER | 805
J8 | JUMPER | JUMPER | 805
LED1 | White | LED-0805 | LED-805
LED3 | Green | LED-0805 | LED-805
LED4 | Red | LED-0805 | LED-805
LED5 | Yellow | LED-0805 | LED-805
LED6 | Red | LED-0805 | LED-805
LED7 | Green | LED-0805 | LED-805
LED8 | Purple | LED-0805 | LED-805
LED9 | Yellow | LED-0805 | LED-805
LED10 | Red | LED-0805 | LED-805
LED11 | Green | LED-0805 | LED-805
LED12 | Red | LED-0805 | LED-805
LED13 | Red | LED-0805 | LED-805
LED14 | Blue | LED-0805 | LED-805
LED17 | Red | LED-0805 | LED-805
LED18 | Red | LED-0805 | LED-805
MTK3339_BREAKOUT |  | M09 | 1X09
P1 | SOLDER_PAD | SOLDER_PAD | SOLDER_PAD_XSMALL
P2 | SOLDER_PAD | SOLDER_PAD | SOLDER_PAD_XSMALL
Q1 | P-CHANNEL_MOSFET_DMP3099L-7 | P-CHANNEL_MOSFET_DMP3099L-7 | SOT23
Q2 |  | DMG3406LSOT | SOT23
Q9 |  | DMG3406LSOT | SOT23
Q10 |  | DMG3406LSOT | SOT23
Q11 |  | DMG3406LSOT | SOT23
Q12 | P-CHANNEL_MOSFET_DMP3099L-7 | P-CHANNEL_MOSFET_DMP3099L-7 | SOT23
R1 | 1K | RESISTOR0805-RES | 805
R2 | 2K | RESISTOR0805-RES | 805
R3 | 1K | RESISTOR0805-RES | 805
R4 | 2K | RESISTOR0805-RES | 805
R5 | 43k | RESISTOR0805-RES | 805
R6 | 12k | RESISTOR0805-RES | 805
R7 | 43k | RESISTOR0805-RES | 805
R8 | 12k | RESISTOR0805-RES | 805
R9 | 10k | RESISTOR0805-RES | 805
R10 | 10k | RESISTOR0805-RES | 805
R11 | 43k | RESISTOR0805-RES | 805
R12 | 10k | RESISTOR0805-RES | 805
R13 | 1k | RESISTOR0805-RES | 805
R14 | 2k | RESISTOR0805-RES | 805
R15 | 43k | RESISTOR0805-RES | 805
R16 | 1.2k | RESISTOR0805-RES | 805
R17 | 20k | RESISTOR0805-RES | 805
R18 | 2k | RESISTOR0805-RES | 805
R19 | 10k | RESISTOR0805-RES | 805
R20 | 270 | RESISTOR0805-RES | 805
R21 | 12k | RESISTOR0805-RES | 805
R22 | 12k | RESISTOR0805-RES | 805
R23 | 43k | RESISTOR0805-RES | 805
R24 | 10k | RESISTOR0805-RES | 805
R25 | 1.2k | RESISTOR0805-RES | 805
R26 | 1.2K | RESISTOR0805-RES | 805
R27 | 10k | RESISTOR0805-RES | 805
R28 | 10k | RESISTOR0805-RES | 805
R29 | 12k | RESISTOR0805-RES | 805
R30 | 33 | RESISTOR0805-RES | 805
R31 | 6.8k | RESISTOR0805-RES | 805
R32 | 1.2k | RESISTOR0805-RES | 805
R33 | 4.7k | RESISTOR0805-RES | 805
R34 | 4.7k | RESISTOR0805-RES | 805
R35 | 150 | RESISTOR0805-RES | 805
R36 | 150 | RESISTOR0805-RES | 805
R37 | 0 | RESISTOR0805-RES | 805
R38 | 150 | RESISTOR0805-RES | 805
R39 | 150 | RESISTOR0805-RES | 805
R40 | 150 | RESISTOR0805-RES | 805
R41 | 150 | RESISTOR0805-RES | 805
R42 | 150 | RESISTOR0805-RES | 805
R43 | 150 | RESISTOR0805-RES | 805
R44 | 0 | RESISTOR0805-RES | 805
R45 | 0 | RESISTOR0805-RES | 805
R46 | 120 | RESISTOR0805-RES | 805
R47 | 10k | RESISTOR0805-RES | 805
R48 | 10k | RESISTOR0805-RES | 805
R49 | 120 | RESISTOR0805-RES | 805
R50 | 10k | RESISTOR0805-RES | 805
R51 | 1.2k | RESISTOR0805-RES | 805
R52 | 1.2k | RESISTOR0805-RES | 805
R53 | 10k | RESISTOR0805-RES | 805
R54 | 5.1k | RESISTOR0805-RES | 805
R55 | 2k | RESISTOR0805-RES | 805
R56 | 33 | RESISTOR0805-RES | 805
R57 | 43k | RESISTOR0805-RES | 805
R58 | 12k | RESISTOR0805-RES | 805
R59 | 43k | RESISTOR0805-RES | 805
R60 | 12k | RESISTOR0805-RES | 805
R61 | 43k | RESISTOR0805-RES | 805
R62 | 12k | RESISTOR0805-RES | 805
R63 | 20 | RESISTOR0805-RES | 805
REG | 5V | OKI-78SR-5 | OKI-78SR
REG1 | LM3940 | LM3940 | SOT223
REG3 | 5V | OKI-78SR-5 | OKI-78SR
S1 |  | BTN_10-XXSMD | TACTILE_SWITCH_SMD_6.2MM_TALL
SOFTWARE_SHUTDOWN_RLY | G5LE | G5LE | ZF112
U$1 | TEENSY_3.2_SIMPLE | TEENSY_3.2_SIMPLE | TEENSY_3.2_SIMPLE
U$2 | TEENSY_3.5_EXT | TEENSY_3.5_EXT | TEENSY_3.5_EXT
U$3 | XBEE | XBEE | XBEE
U$4 | N-CHANNEL_MOSFET_FQP30N06L | N-CHANNEL_MOSFET_HOR_HOLE | TO-220-H-HOLE
U$5 | MC34152 | MC34152 | SOIC-08
U$6 | N-CHANNEL_MOSFET_FQP30N06L | N-CHANNEL_MOSFET_HOR_HOLE | TO-220-H-HOLE
U$7 | N-CHANNEL_MOSFET_FQP30N06L | N-CHANNEL_MOSFET_HOR_HOLE | TO-220-H-HOLE
U$8 | TEST_POINT | TEST_POINT | TEST_POINT
U$9 | ACS715_CURRENT_SENSOR | ACS715_CURRENT_SENSOR | SOP8
U$10 | ACS715_CURRENT_SENSOR | ACS715_CURRENT_SENSOR | SOP8
U$11 | TEST_POINT | TEST_POINT | TEST_POINT
U$12 | TEST_POINT | TEST_POINT | TEST_POINT
U$16 | CR-2450/G1AN | CR-2450/G1AN | CR-2450/G1AN
U$17 | MCP23S17SSOP28 | MCP23S17SSOP28 | SSOP28
U$18 | MCP3208SOIC | MCP3208SOIC | SOIC-16
U$19 | MC34152 | MC34152 | SOIC-08
U$20 | MCP6002SOIC | MCP6002SOIC | SOIC-08
U$21 |  | MAX7480 | SOIC-08
U$22 |  | MAX7480 | SOIC-08
U$23 | MCP6002SOIC | MCP6002SOIC | SOIC-08
U$24 | MCP6002SOIC | MCP6002SOIC | SOIC-08
U$25 | TXB0104TSSOP | TXB0104TSSOP | TSSOP-14
U$26 |  | MAX7480 | SOIC-08
U$27 |  | MAX7480 | SOIC-08
U$28 |  | MAX7480 | SOIC-08
U$29 | TLP291-4 | TLP291-4 | 11-11F1
U$30 | TLP291-4 | TLP291-4 | 11-11F1
X1 | CONNECTOR-37 | CONNECTOR-37 | AUTOSPORT_14-35
X2 | CONNECTOR-4AUTOSPORT | CONNECTOR-4AUTOSPORT | AUTOSPORT_12-04
X3 | CONNECTOR-4NANO-FIT-VERTICAL-4 | CONNECTOR-4NANO-FIT-VERTICAL-4 | NANO-FIT_VERTICAL-4
X4 | CONNECTOR-4NANO-FIT-VERTICAL-4 | CONNECTOR-4NANO-FIT-VERTICAL-4 | NANO-FIT_VERTICAL-4
